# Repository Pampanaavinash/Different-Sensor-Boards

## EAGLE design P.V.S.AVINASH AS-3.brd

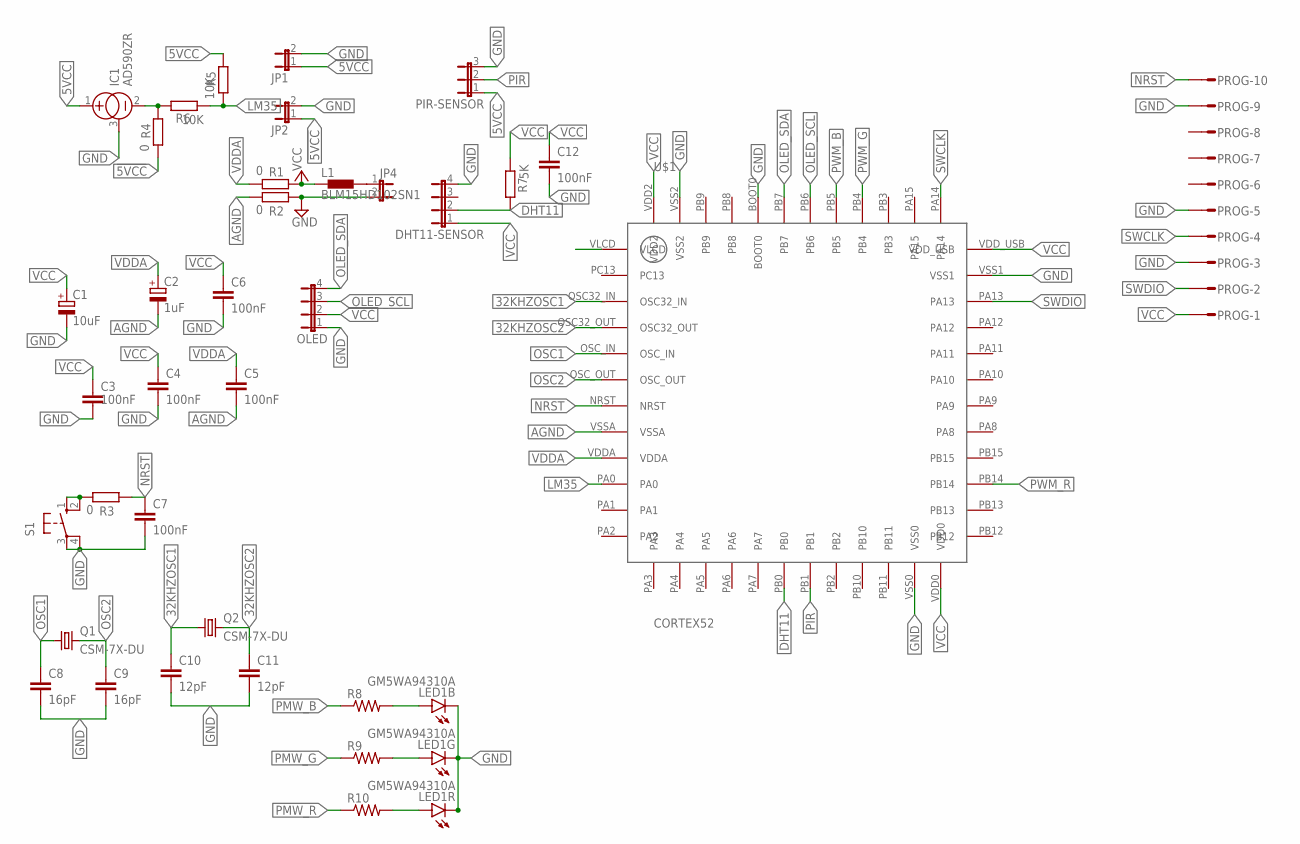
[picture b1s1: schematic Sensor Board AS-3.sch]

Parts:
C1: 10uF; 139CLL-2R
C2: 1uF; 139CLL-2R
C3, C4, C5, C6, C7, C12: 100nF; C0805
C8, C9: 16pF; C0805
C10, C11: 12pF; C0805
DHT11-SENSOR: JP4E; JP4
IC1: AD590ZR; TO92
JP1, JP2, JP4: JP1E; JP1
L1: BLM15HD102SN1; 0402
LED1: GM5WA94310A
OLED: JP4E; JP4
PIR-SENSOR: JP2E; JP2
PROG: S10P
Q1, Q2: CSM-7X-DU
R1, R2, R3, R4: 0; R0805
R5, R6: 10K; R0805
R7: 5K; R0805
R8, R9, R10: R-US_R0805; R0805
S1: 10-XX; B3F-10XX
U$1: CORTEX52

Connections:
5VCC: IC1.1 (+), JP1.1, PIR-SENSOR.1, R5.2
32KHZOSC1: C10.1, Q2.1, U$1.OSC32_IN
32KHZOSC2: C11.1, Q2.2, U$1.OSC32_OUT
!5VCC: JP2.1, R4.1
AGND: C2.-, C5.2, R2.1, U$1.VSSA
DHT11: DHT11-SENSOR.2, R7.2, U$1.PB0
GND: C1.-, C3.2, C4.2, C6.2, C7.2, C8.2, C9.2, C10.2, C11.2, C12.2, DHT11-SENSOR.4, IC1.3 (CAN), JP1.2, JP2.2, JP4.2, LED1.4 (C), LED1.5 (C), LED1.6 (C), OLED.1, PIR-SENSOR.3, PROG.3, PROG.5, PROG.9, R2.2, S1.3, S1.4 (P1), U$1.BOOT0, U$1.VSS0, U$1.VSS1, U$1.VSS2
LM35: R5.1, R6.1, U$1.PA0
unnamed: JP4.1, L1.2
unnamed: R3.1, S1.1 (S), S1.2 (S1)
unnamed: IC1.2 (-), R4.2, R6.2
unnamed: LED1.1 (A), R8.2
unnamed: LED1.3 (A), R9.2
unnamed: LED1.2 (A), R10.2
NRST: C7.1, PROG.10, R3.2, U$1.NRST
OLED_SCL: OLED.3, U$1.PB6
OLED_SDA: OLED.4, U$1.PB7
OSC1: C8.1, Q1.1, U$1.OSC_IN
OSC2: C9.1, Q1.2, U$1.OSC_OUT
PIR: PIR-SENSOR.2, U$1.PB1
PMW_B: R8.1
PMW_G: R9.1
PMW_R: R10.1
PWM_B: U$1.PB5
PWM_G: U$1.PB4
PWM_R: U$1.PB14
SWCLK: PROG.4, U$1.PA14
SWDIO: PROG.2, U$1.PA13
VCC: C1.+, C3.1, C4.1, C6.1, C12.1, DHT11-SENSOR.1, L1.1, OLED.2, PROG.1, R1.2, R7.1, U$1.VDD0, U$1.VDD2, U$1.VDD_USB
VDDA: C2.+, C5.1, R1.1, U$1.VDDA

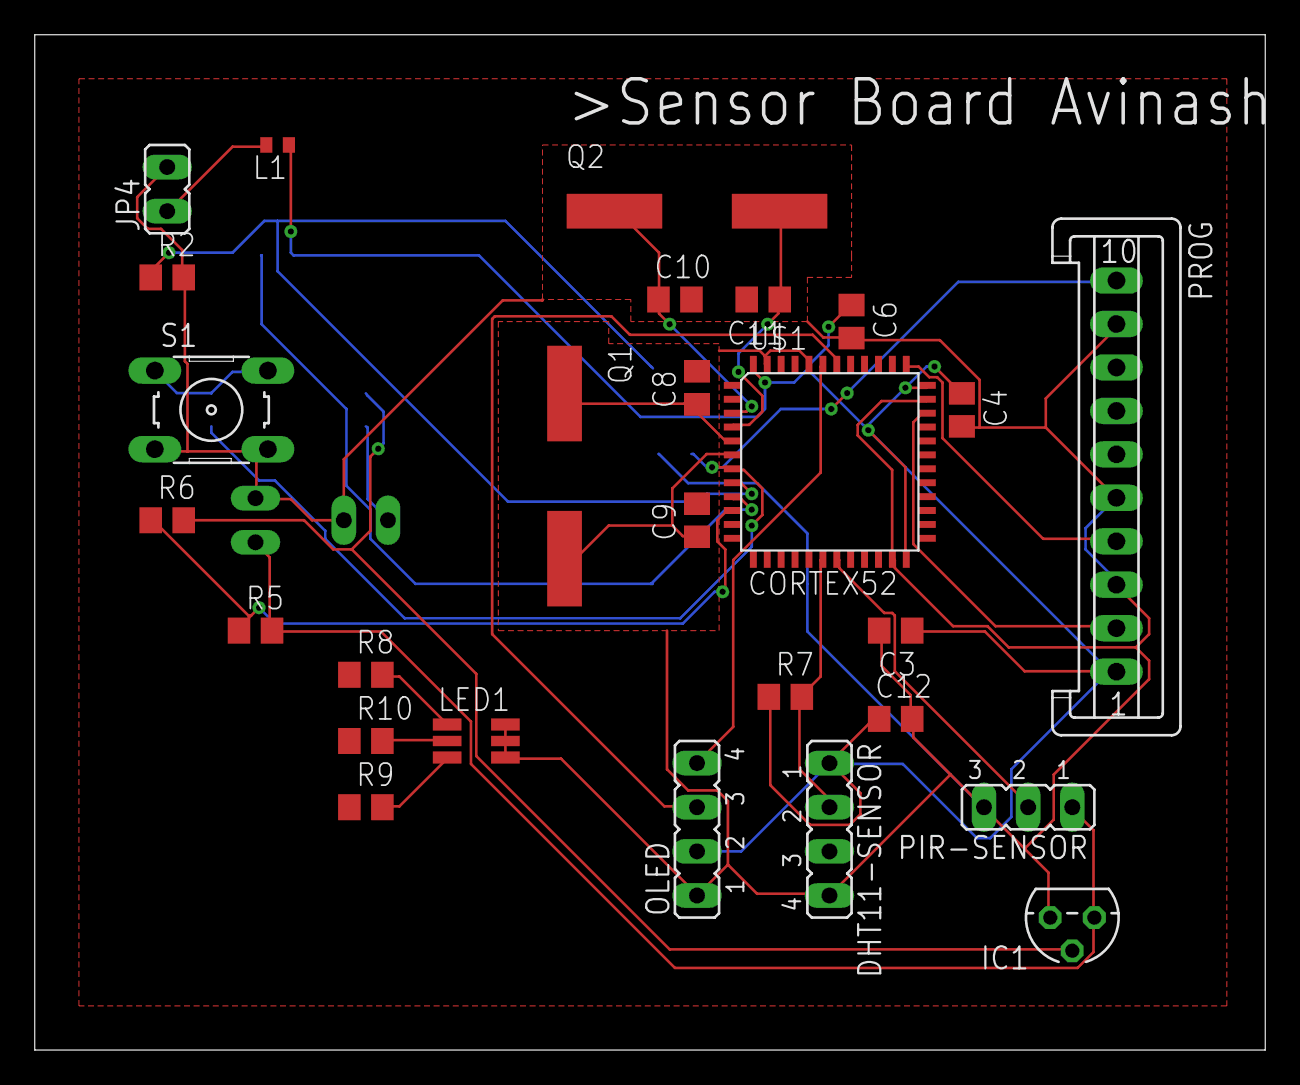
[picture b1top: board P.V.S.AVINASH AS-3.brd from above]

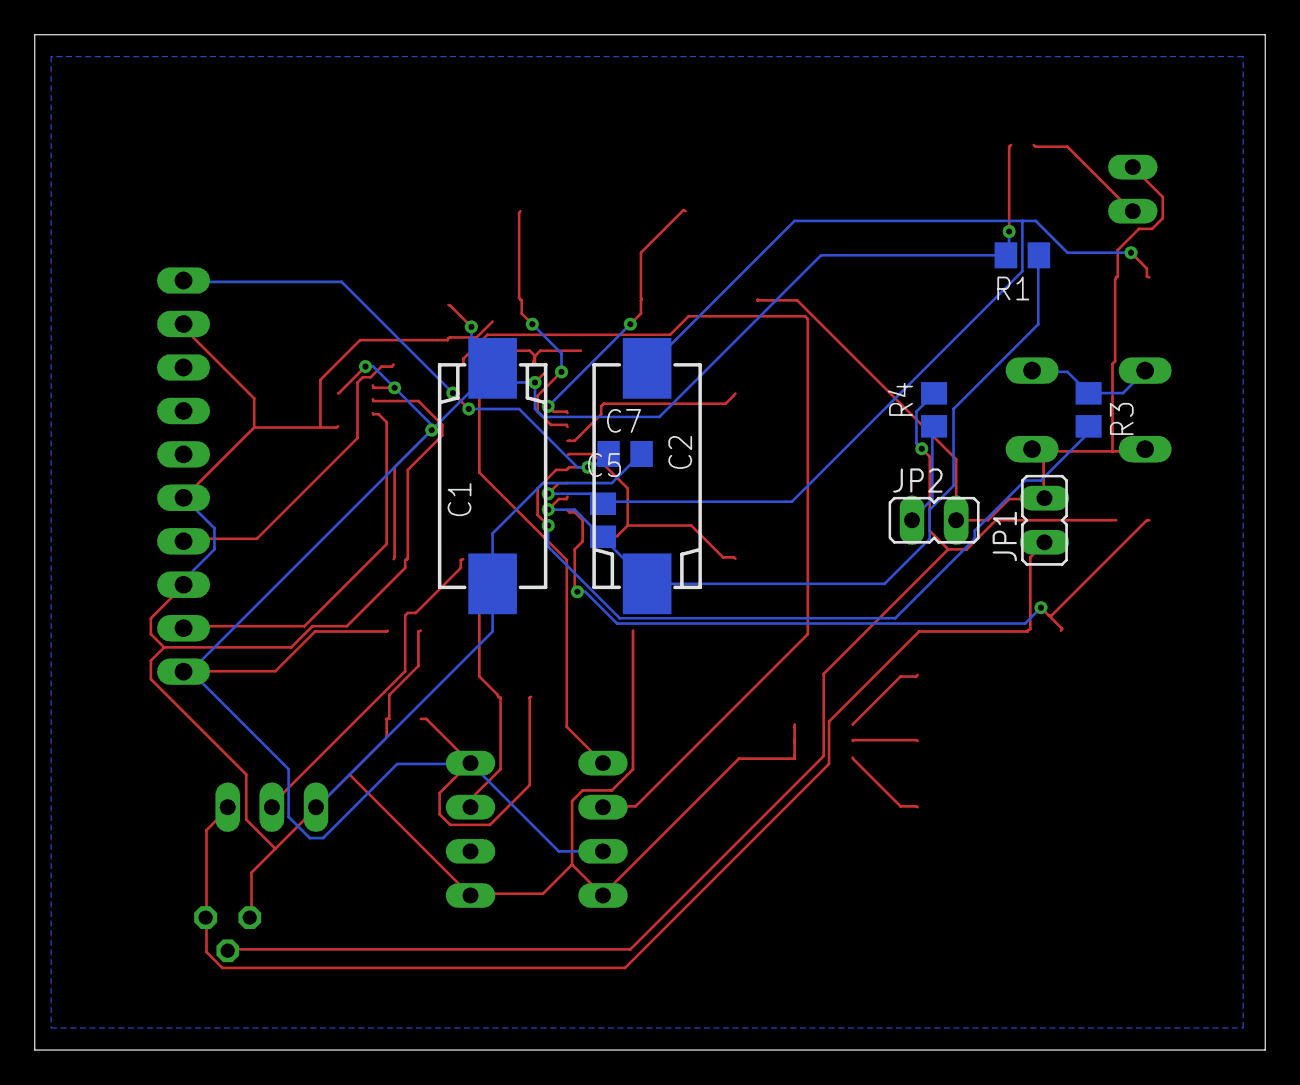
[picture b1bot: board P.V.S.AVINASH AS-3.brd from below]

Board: 2 copper layers, 70.8 x 58.4 mm, 36 parts (9 on the bottom side), 24 nets.
